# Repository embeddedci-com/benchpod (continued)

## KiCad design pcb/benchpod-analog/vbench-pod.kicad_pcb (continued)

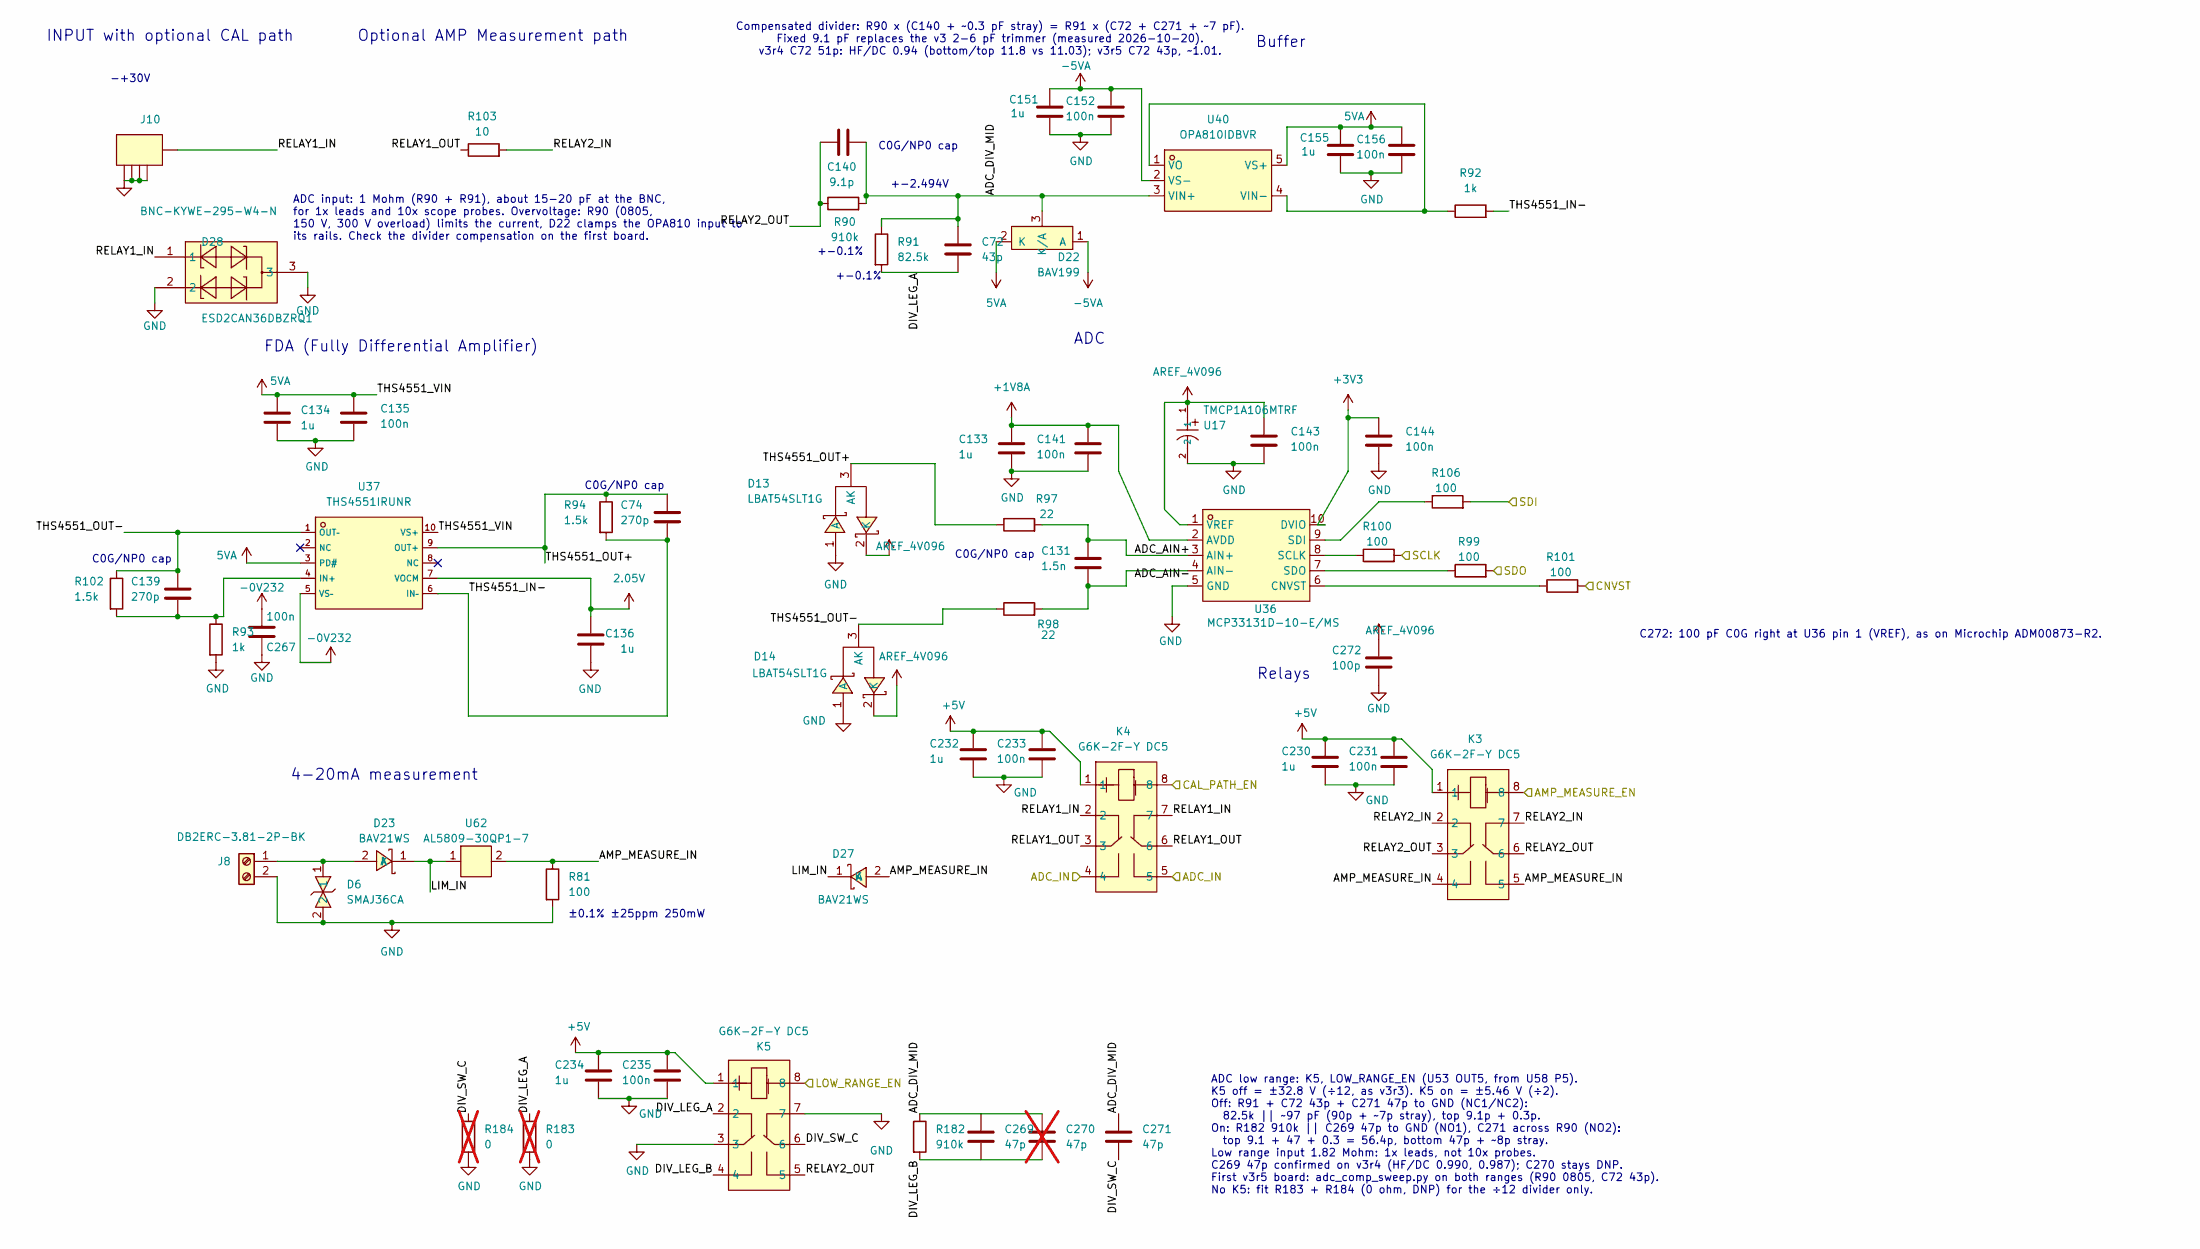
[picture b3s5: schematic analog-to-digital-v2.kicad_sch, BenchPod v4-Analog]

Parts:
C72: 43p; C_0402_1005Metric; LCSC C415393
C74, C139: 270p; C_0402_1005Metric; LCSC C161545
C131: 1.5n; C_0402_1005Metric; LCSC C668348
C133, C136: 1u; C_0402_1005Metric; MPN GRM155R61H105KE05D; LCSC C1518208
C134, C151, C155, C230, C232, C234: 1u; C_0402_1005Metric; MPN CL05A105KA5NQNC; LCSC C52923
C135, C141, C143, C144, C152, C156, C231, C233, C235: 100n; C_0402_1005Metric; MPN CC0603KRX7R9BB104; LCSC C307331
C140: 9.1p; C_0603_1608Metric; MPN GQM1875C2E9R1BB12D; LCSC C2299929
C267: 100n; C_0402_1005Metric; LCSC C307331
C269: 47p; C_0402_1005Metric; LCSC C277503
C270: 47p; C_0402_1005Metric; LCSC C277503; not fitted
C271: 47p; C_0603_1608Metric; LCSC C882574
C272: 100p; C_0402_1005Metric; MPN 0402CG101J500NT; LCSC C1546
D6: SMAJ36CA; SMA_L4.3-W2.6-LS5.0-BI; MPN SMAJ36CA; LCSC Part C5353135
D13, D14: LBAT54SLT1G; SOT-23_L2.9-W1.3-P1.90-LS2.4-BR; MPN LBAT54SLT1G; LCSC Part C12765
D22: BAV199; C145516_SOT-23_L2.9-W1.3-P1.90-LS2.4-BR; LCSC C145516
D23, D27: BAV21WS; D_SOD-323; MPN BAV21WS; LCSC Part C7420334
D28: ESD2CAN36DBZRQ1; SOT-23; LCSC C36382904
J8: DB2ERC-3.81-2P-BK; C5259145_CONN-TH_2P-P3.81_DB2ERC-3.81-2P-BK; MFR. Part # DB2ERC-3.81-2P-BK; LCSC Part # C5259145
J10: BNC-KYWE-295-W4-N; C41416668_BNC-TH_BNC-KYWE-295-W4-N; LCSC C41416668
K3, K4, K5: G6K-2F-Y DC5; RELAY-TH_G6K-2F-Y; MPN G6K-2F-Y-TR DC5 BY OMR/C; LCSC Part C231390
R81: 100; R_1206_3216Metric; LCSC C728670
R90: 910k; R_0805_2012Metric; LCSC C865698
R91: 82.5k; R_0603_1608Metric; LCSC C705796
R92, R93: 1k; R_0402_1005Metric; LCSC C852624
R94, R102: 1.5k; R_0402_1005Metric; LCSC C281775
R97, R98: 22; R_0402_1005Metric; LCSC C25092
R99, R100, R101, R106: 100; R_0402_1005Metric; LCSC C25076
R103: 10; R_0402_1005Metric; LCSC C25077
R182: 910k; R_0603_1608Metric; LCSC C2686431
R183, R184: 0; R_0603_1608Metric; LCSC C21189; not fitted
U17: TMCP1A106MTRF; C1969735_CAP-SMD_L2_0-W1_3-FD; LCSC C1969735
U36: MCP33131D-10-E/MS; MSOP-10_L3.0-W3.0-P0.50-LS5.0-BL; MPN MCP33131D-10-E/MS; LCSC Part C635978
U37: THS4551IRUNR; C2060364_QFN-10_L2_0-W2_0-P0_50-BL; LCSC C2060364
U40: OPA810IDBVR; SOT-23-5_L2.9-W1.6-P0.95-LS2.8-TL; MPN OPA810IDBVR; LCSC Part C2833513
U62: AL5809-30QP1-7; POWERDI-123_L2.7-W1.6-LS3.7-RD; MPN AL5809-30QP1-7; LCSC Part C2678648

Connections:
2.05V: C136.2, U37.7 (VOCM); also elsewhere on the board
5VA: C134.2, C135.2, C155.2, C156.2, D22.2 (K), U37.3 (PD#), U37.10 (VS+), U40.5 (VS+); also elsewhere on the board
+1V8A: C133.2, C141.2, U36.2 (AVDD); also elsewhere on the board
+3V3: C144.2, U36.10 (DVIO); also elsewhere on the board
+5V: C230.2, C231.2, C232.2, C233.2, C234.2, C235.2, K3.1, K4.1, K5.1; also elsewhere on the board
-5VA: C151.2, C152.2, D22.1 (A), U40.2 (VS-); also elsewhere on the board
/ADC_CNVST: R101.2; also elsewhere on the board
/ADC_SCLK: R100.2; also elsewhere on the board
/ADC_SDI: R106.2; also elsewhere on the board
/ADC_SDO: R99.2; also elsewhere on the board
/AMP_MEAS_EN: K3.8; also elsewhere on the board
/CAL_PATH_EN: K4.8; also elsewhere on the board
/DAC_TO_ADC: K4.4, K4.5; also elsewhere on the board
/LOW_RANGE_EN: K5.8; also elsewhere on the board
/analog to digital v2/ADC_AIN+: C131.1, R97.2, U36.3 (AIN+)
/analog to digital v2/ADC_AIN-: C131.2, R98.2, U36.4 (AIN-)
/analog to digital v2/ADC_DIV_MID: C72.1, C140.2, C269.1, C270.1, C271.1, D22.3 (K/A), R90.2, R91.1, R182.1, U40.3 (VIN+)
/analog to digital v2/AMP_MEASURE_IN: D27.2 (A), K3.4, K3.5, R81.1, U62.2 (Out)
/analog to digital v2/DIV_LEG_A: C72.2, K5.2, R91.2, R183.1
/analog to digital v2/DIV_LEG_B: C269.2, C270.2, K5.4, R182.2
/analog to digital v2/DIV_SW_C: C271.2, K5.6, R184.1
/analog to digital v2/LIM_IN: D23.1 (K), D27.1 (K), U62.1 (In)
/analog to digital v2/RELAY1_IN: D28.1, J10.5 (OUT), K4.2, K4.7
/analog to digital v2/RELAY1_OUT: K4.3, K4.6, R103.1
/analog to digital v2/RELAY2_IN: K3.2, K3.7, R103.2
/analog to digital v2/RELAY2_OUT: C140.1, K3.3, K3.6, K5.5, R90.1
/analog to digital v2/THS4551_IN-: C74.2, R92.2, R94.2, U37.6 (IN–)
/analog to digital v2/THS4551_OUT+: C74.1, D13.3 (AK), R94.1, R97.1, U37.9 (OUT+)
/analog to digital v2/THS4551_OUT-: C139.1, D14.3 (AK), R98.1, R102.1, U37.1 (OUT–)
AREF_4V096: C143.2, C272.1, D13.2 (K), D14.2 (K), U17.1, U36.1 (VREF); also elsewhere on the board
GND: C133.1, C134.1, C135.1, C136.1, C141.1, C143.1, C144.1, C151.1, C152.1, C155.1, C156.1, C230.1, C231.1, C232.1, C233.1, C234.1, C235.1, C267.2, C272.2, D6.2, D13.1 (A), D14.1 (A), D28.2, D28.3, J8.2, J10.1 (GND), J10.2 (GND), J10.3 (GND), J10.4 (GND), K5.3, K5.7, R81.2, R93.2, R183.2, R184.2, U17.2, U36.5 (GND); also elsewhere on the board
unnamed: D6.1, D23.2 (A), J8.1
unnamed: R101.1, U36.6 (CNVST)
unnamed: R100.1, U36.8 (SCLK)
unnamed: R106.1, U36.9 (SDI)
unnamed: R99.1, U36.7 (SDO)
unnamed: C139.2, R93.1, R102.2, U37.4 (IN+)
unnamed: R92.1, U40.1 (VO), U40.4 (VIN-)
−0V232: C267.1, U37.5 (VS–); also elsewhere on the board

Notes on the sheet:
C0G/NP0 cap
4-20mA measurement
+-0.1%
ADC
+-2.494V
Buffer
±0.1% ±25ppm 250mW
Optional AMP Measurement path
Relays
C272: 100 pF C0G right at U36 pin 1 (VREF), as on Microchip ADM00873-R2.
ADC input: 1 Mohm (R90 + R91), about 15-20 pF at the BNC, for 1x leads and 10x scope probes. Overvoltage: R90 (0805, 150 V, 300 V overload) limits the current, D22 clamps the OPA810 input to its rails. Check the divider compensation on the first board.
FDA (Fully Differential Amplifier)
INPUT with optional CAL path
-+30V
Compensated divider: R90 x (C140 + ~0.3 pF stray) = R91 x (C72 + C271 + ~7 pF). Fixed 9.1 pF replaces the v3 2-6 pF trimmer (measured 2026-10-20). v3r4 C72 51p: HF/DC 0.94 (bottom/top 11.8 vs 11.03); v3r5 C72 43p, ~1.01.
ADC low range: K5, LOW_RANGE_EN (U53 OUT5, from U58 P5). K5 off = ±32.8 V (÷12, as v3r3). K5 on = ±5.46 V (÷2). Off: R91 + C72 43p + C271 47p to GND (NC1/NC2): 82.5k || ~97 pF (90p + ~7p stray), top 9.1p + 0.3p. On: R182 910k || C269 47p to GND (NO1), C271 across R90 (NO2): top 9.1 + 47 + 0.3 = 56.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

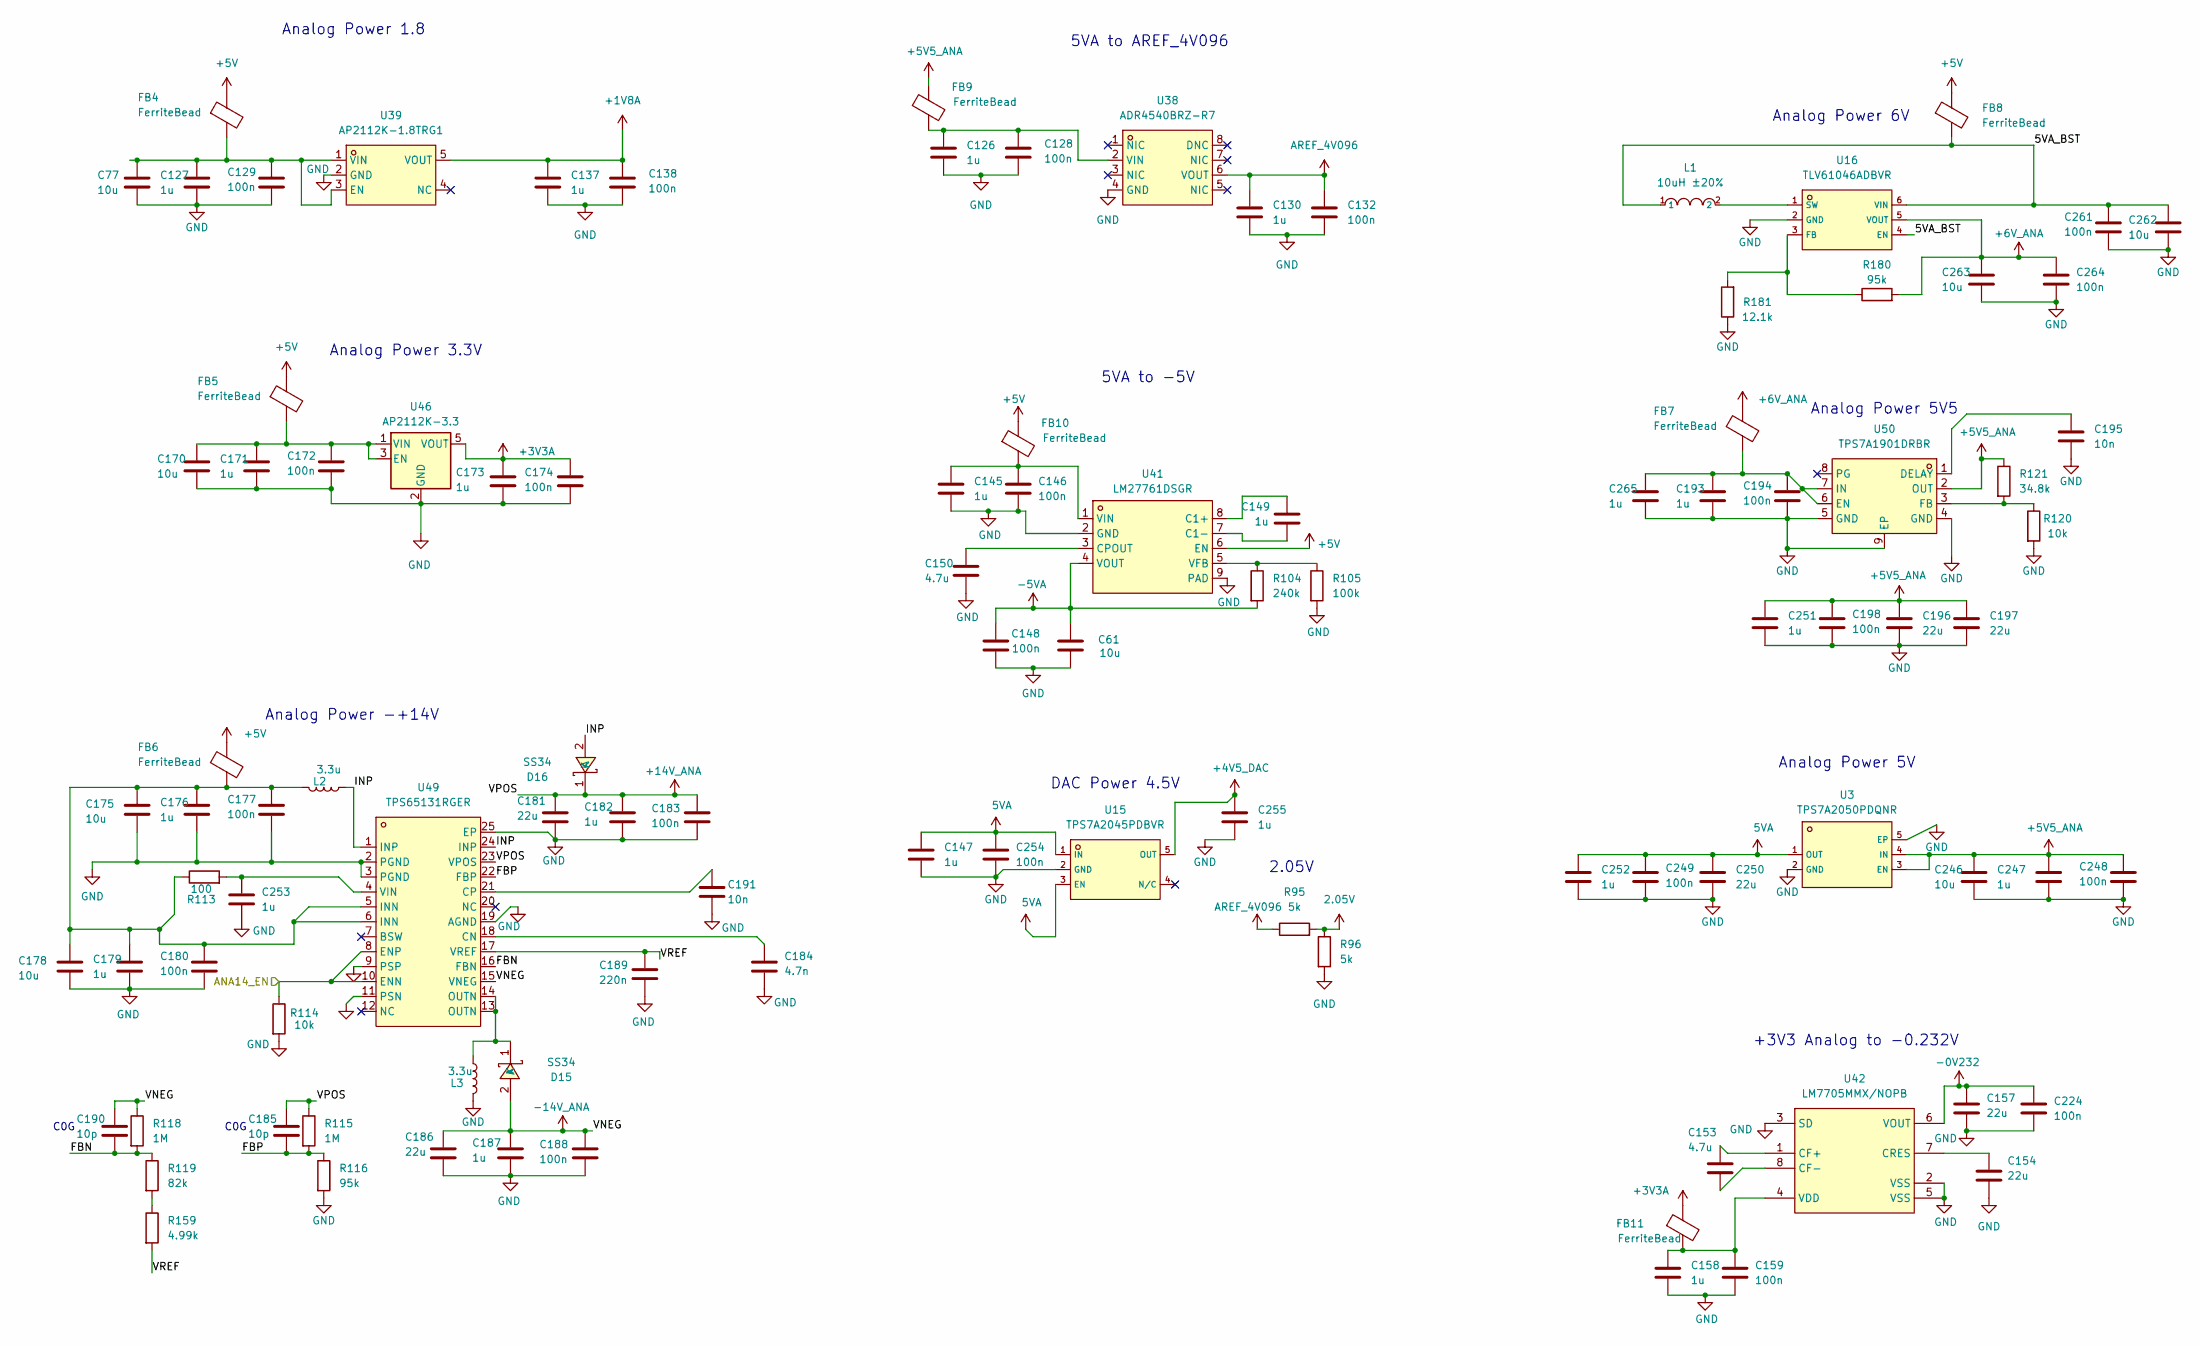
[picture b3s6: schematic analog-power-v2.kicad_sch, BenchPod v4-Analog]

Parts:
C61: 10u; C_0603_1608Metric; LCSC C96446
C77, C170, C175, C178, C246, C262, C263: 10u; C_0603_1608Metric; MPN GRM21BR61H106KE43L; LCSC C96446
C126, C130, C137, C145, C149, C158, C173, C176, C179, C182, C187, C193, C253, C255, C265: 1u; C_0402_1005Metric; MPN GRM155R61H105KE05D; LCSC C1518208
C127, C147, C171, C247, C251, C252: 1u; C_0402_1005Metric; MPN CL05A105KA5NQNC; LCSC C52923
C128, C129, C132, C138, C146, C148, C159, C172, C174, C177, C180, C183, C188, C194, C198, C224, C248, C249, C254, C261, C264: 100n; C_0402_1005Metric; MPN CC0603KRX7R9BB104; LCSC C307331
C150, C153: 4.7u; C_0805_2012Metric; LCSC C98192
C154, C157, C196, C197, C250: 22u; C_0805_2012Metric; LCSC C45783
C181, C186: 22u; C_0805_2012Metric; MPN CL21B105KBFNNNE; LCSC C45783
C184: 4.7n; C_0402_1005Metric; MPN CC0603KRX7R9BB104; LCSC C1538
C185, C190: 10p; C_0402_1005Metric; LCSC C32949
C189: 220n; C_0603_1608Metric; LCSC C64705
C191, C195: 10n; C_0402_1005Metric; LCSC C15195
D15, D16: SS34; SMA_L4.3-W2.6-LS5.2-RD; MPN SS34; LCSC Part C3014011
FB4, FB5, FB6, FB7, FB8, FB9, FB10, FB11: FerriteBead; C85833_L0603; LCSC C85833
L1: 10uH ±20%; C38117_IND-SMD_L4_0-W4_0; LCSC C38117
L2, L3: 3.3u; IND-SMD_L2.0-W1.6_AOTA-B201610S3R3-101-T; LCSC C42411119
R95, R96: 5k; R_0402_1005Metric; LCSC C5948099
R104: 240k; R_0402_1005Metric; LCSC C64043
R105: 100k; R_0402_1005Metric; LCSC C25741
R113: 100; R_0402_1005Metric; LCSC C25076
R114, R120: 10k; R_0402_1005Metric; LCSC C25744
R115, R118: 1M; R_0603_1608Metric; LCSC C22935
R116, R180: 95k; R_0402_1005Metric; LCSC C22375098
R119: 82k; R_0603_1608Metric; LCSC C23254
R121: 34.8k; R_0402_1005Metric; LCSC C2998092
R159: 4.99k; R_0603_1608Metric; LCSC C23046
R181: 12.1k; R_0402_1005Metric; LCSC C25852
U3: TPS7A2050PDQNR; C2866499_X2SON-4_L1_0-W1_0-P0_65-TL-EP; LCSC C2866499
U15: TPS7A2045PDBVR; C2873627_SOT-23-5_L2_9-W1_6-P0_95-LS2_8-BR; LCSC C2873627
U16: TLV61046ADBVR; C464815_SOT-23-6_L2_9-W1_6-P0_95-LS2_8-BL; LCSC C464815
U38: ADR4540BRZ-R7; SOIC-8_L4.9-W3.9-P1.27-LS6.0-BL; MPN ADR4540BRZ-R7; LCSC Part C404003
U39: AP2112K-1.8TRG1; SOT-25_L3.0-W1.6-P0.95-LS2.8-BL; MPN AP2112K-1.8TRG1; LCSC Part C176944
U41: LM27761DSGR; WSON-8_L2.0-W2.0-P0.65-BL-EP; MPN LM27761DSGR; LCSC Part C129351
U42: LM7705MMX/NOPB; MSOP-8_L3.0-W3.0-P0.65-LS5.0-BL; MPN LM7705MMX/NOPB; LCSC Part C2070761
U46: AP2112K-3.3; SOT-25-5_L2.9-W1.6-P0.95-LS2.8-BL; LCSC C51118
U49: TPS65131RGER; VQFN-24_L4.0-W4.0-P0.50-BL-EP2.5; LCSC Part C87663
U50: TPS7A1901DRBR; TDFN-8_L3.0-W3.0-P0.65-BL-EP; MPN TPS7A1901DRBR; LCSC Part C544334

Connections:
2.05V: R95.2, R96.1; also elsewhere on the board
5VA: C147.2, C249.2, C250.1, C252.2, C254.2, U3.1 (OUT), U15.1 (IN), U15.3 (EN); also elsewhere on the board
+1V8A: C137.2, C138.2, U39.5 (VOUT); also elsewhere on the board
+3V3A: C173.2, C174.2, FB11.1, U46.5 (VOUT); also elsewhere on the board
+4V5_DAC: C255.2, U15.5 (OUT); also elsewhere on the board
+5V: FB4.1, FB5.1, FB6.1, FB8.1, FB10.1, U41.6 (EN); also elsewhere on the board
+5V5_ANA: C196.1, C197.1, C198.2, C246.2, C247.2, C248.2, C251.2, FB9.1, R121.1, U3.3 (EN), U3.4 (IN), U50.2 (OUT); also elsewhere on the board
+6V_ANA: C263.2, C264.2, FB7.1, R180.2, U16.5 (VOUT)
+14V_ANA: C181.2, C182.2, C183.2, C185.1, D16.1 (K), R115.1, U49.23 (VPOS); also elsewhere on the board
-5VA: C61.1, C148.2, R104.2, U41.4 (VOUT); also elsewhere on the board
-14V_ANA: C186.2, C187.2, C188.2, C190.1, D15.2 (A), R118.1, U49.15 (VNEG); also elsewhere on the board
/ANA14_EN: R114.1, U49.8 (ENP), U49.10 (ENN); also elsewhere on the board
/Analog Power v2/5VA_BST: C261.2, C262.2, FB8.2, L1.1, U16.4 (EN), U16.6 (VIN)
/Analog Power v2/FBN: C190.2, R118.2, R119.1, U49.16 (FBN)
/Analog Power v2/FBP: C185.2, R115.2, R116.1, U49.22 (FBP)
/Analog Power v2/INP: D16.2 (A), L2.1, U49.1 (INP), U49.24 (INP)
/Analog Power v2/VREF: C189.2, R159.2, U49.17 (VREF)
AREF_4V096: C130.2, C132.2, R95.1, U38.6 (VOUT); also elsewhere on the board
GND: C61.2, C77.1, C126.1, C127.1, C128.1, C129.1, C130.1, C132.1, C137.1, C138.1, C145.1, C146.1, C147.1, C148.1, C150.2, C154.2, C157.2, C158.1, C159.1, C170.1, C171.1, C172.1, C173.1, C174.1, C175.1, C176.1, C177.1, C178.1, C179.1, C180.1, C181.1, C182.1, C183.1, C184.1, C186.1, C187.1, C188.1, C189.1, C191.2, C193.1, C194.1, C195.2, C196.2, C197.2, C198.1, C224.1, C246.1, C247.1, C248.1, C249.1, C250.2, C251.1, C252.1, C253.1, C254.1, C255.1, C261.1, C262.1, C263.1, C264.1, C265.1, L3.2, R96.2, R105.2, R114.2, R116.2, R120.2, R181.1, U3.2 (GND), U3.5 (EP), U15.2 (GND), U16.2 (GND), U38.4 (GND), U39.2 (GND), U41.2 (GND), U41.9 (PAD), U42.2 (VSS), U42.3 (SD), U42.5 (VSS), U46.2 (GND), U49.2 (PGND), U49.3 (PGND), U49.9 (PSP), U49.11 (PSN), U49.19 (AGND), U49.25 (EP), U50.4 (GND), U50.5 (GND), U50.9 (EP); also elsewhere on the board
unnamed: C175.2, C176.2, C177.2, C178.2, C179.2, C180.2, FB6.2, L2.2, R113.1, U49.5 (INN), U49.6 (INN)
unnamed: D15.1 (K), L3.1, U49.13 (OUTN), U49.14 (OUTN)
unnamed: R119.2, R159.1
unnamed: R180.1, R181.2, U16.3 (FB)
unnamed: L1.2, U16.1 (SW)
unnamed: C126.2, C128.2, FB9.2, U38.2 (VIN)
unnamed: C77.2, C127.2, C129.2, FB4.2, U39.1 (VIN), U39.3 (EN)
unnamed: C149.2, U41.8 (C1+)
unnamed: C149.1, U41.7 (C1-)
unnamed: C150.1, U41.3 (CPOUT)
unnamed: R104.1, R105.1, U41.5 (VFB)
unnamed: C145.2, C146.2, FB10.2, U41.1 (VIN)
unnamed: C153.1, U42.1 (CF+)
unnamed: C153.2, U42.8 (CF-)
unnamed: C154.1, U42.7 (CRES)
unnamed: C158.2, C159.2, FB11.2, U42.4 (VDD)
unnamed: C170.2, C171.2, C172.2, FB5.2, U46.1 (VIN), U46.3 (EN)
unnamed: C184.2, U49.18 (CN)
unnamed: C191.1, U49.21 (CP)
unnamed: C253.2, R113.2, U49.4 (VIN)
unnamed: C195.1, U50.1 (DELAY)
unnamed: C193.2, C194.2, C265.2, FB7.2, U50.6 (EN), U50.7 (IN)
unnamed: R120.1, R121.2, U50.3 (FB)
−0V232: C157.1, C224.2, U42.6 (VOUT); also elsewhere on the board

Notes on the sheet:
5VA to AREF_4V096
Analog Power 6V
DAC Power 4.5V
Analog Power 5V
5VA to -5V
Analog Power 5V5
C0G
2.05V
Analog Power 3.3V
Analog Power 1.8
+3V3 Analog to -0.232V
Analog Power -+14V

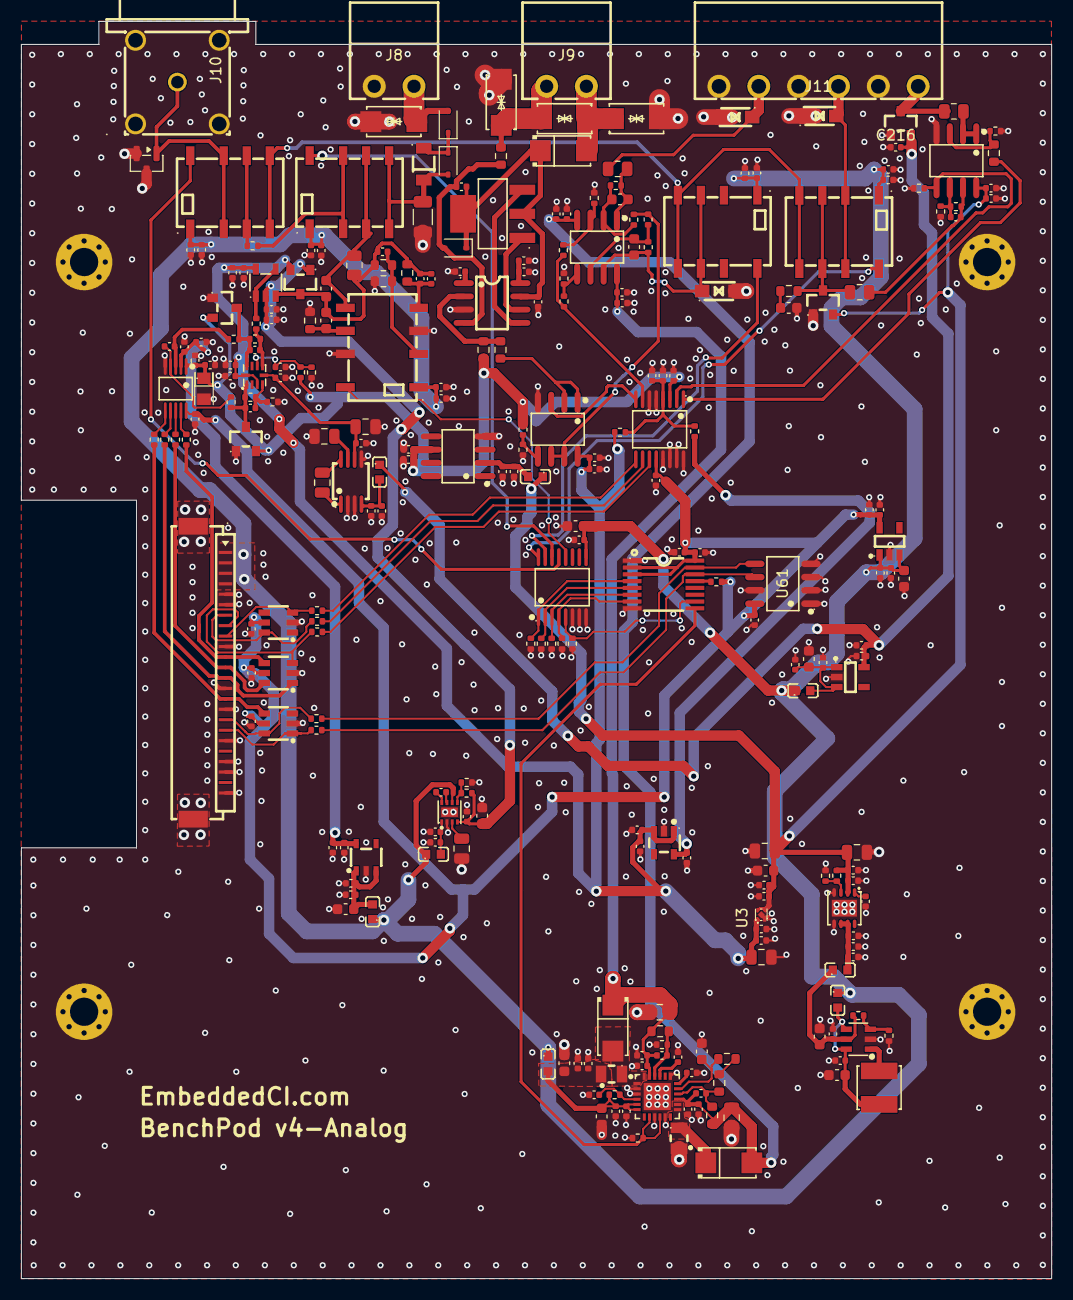
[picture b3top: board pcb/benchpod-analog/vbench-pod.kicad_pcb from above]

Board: 4 copper layers, 98.5 x 120.2 mm, 270 parts (0 on the bottom side), 124 nets.

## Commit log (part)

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2026-06-22 v2.0.0
2026-06-23 rp2350B flash fixes
